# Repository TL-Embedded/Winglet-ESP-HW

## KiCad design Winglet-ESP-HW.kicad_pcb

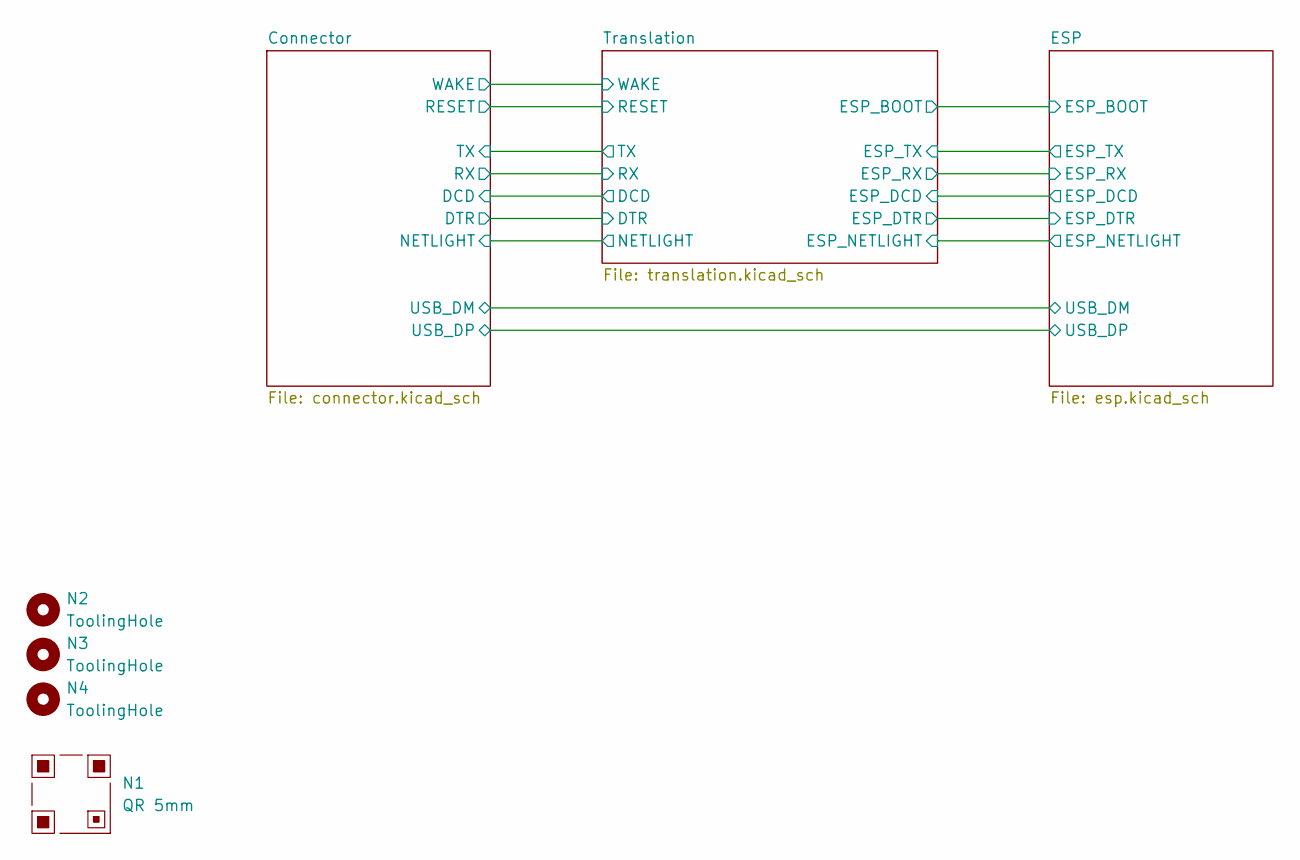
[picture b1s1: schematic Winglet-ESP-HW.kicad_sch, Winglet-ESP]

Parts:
N1: QR 5mm; QR_5mm_JLC
N2, N3, N4: ToolingHole; ToolingHole_1mm

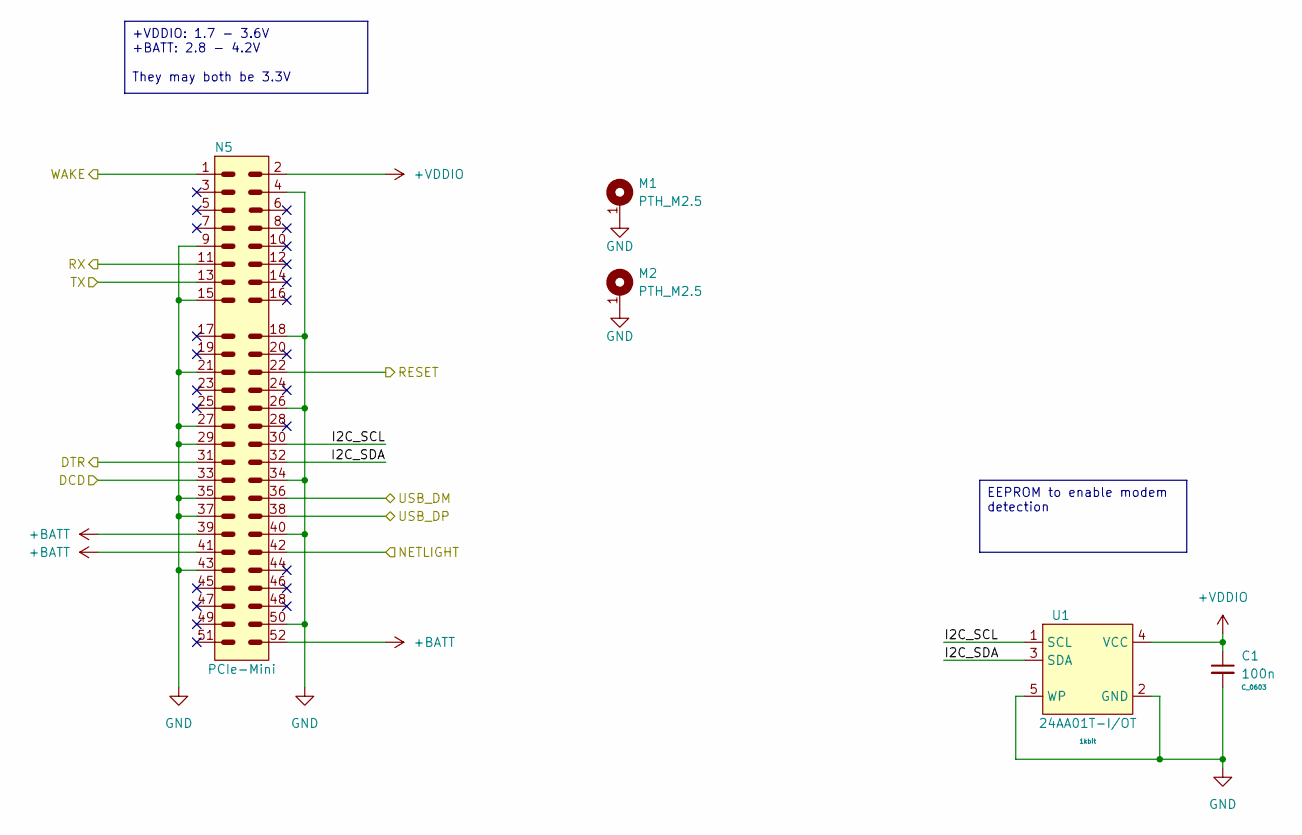
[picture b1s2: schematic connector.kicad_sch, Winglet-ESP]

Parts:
C1: 100n; C_0603
M1, M2: PTH_M2.5
N5: PCIe-Mini
U1: 24AA01T-I/OT; SOT23_5

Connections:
+BATT: N5.39, N5.41, N5.52; also elsewhere on the board
+VDDIO: C1.1, N5.2, U1.4 (VCC); also elsewhere on the board
/Connector/DCD: N5.33; also elsewhere on the board
/Connector/DTR: N5.31; also elsewhere on the board
/Connector/I2C_SCL: N5.30, U1.1 (SCL)
/Connector/I2C_SDA: N5.32, U1.3 (SDA)
/Connector/NETLIGHT: N5.42; also elsewhere on the board
/Connector/RESET: N5.22; also elsewhere on the board
/Connector/RX: N5.11; also elsewhere on the board
/Connector/TX: N5.13; also elsewhere on the board
/Connector/USB_DM: N5.36; also elsewhere on the board
/Connector/USB_DP: N5.38; also elsewhere on the board
/Connector/WAKE: N5.1; also elsewhere on the board
GND: C1.2, M1.1, M2.1, N5.4, N5.9, N5.15, N5.18, N5.21, N5.26, N5.27, N5.29, N5.34, N5.35, N5.37, N5.40, N5.43, N5.50, U1.2 (GND), U1.5 (WP); also elsewhere on the board

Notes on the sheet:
+VDDIO: 1.7 - 3.6V +BATT: 2.8 - 4.2V They may both be 3.3V
EEPROM to enable modem detection

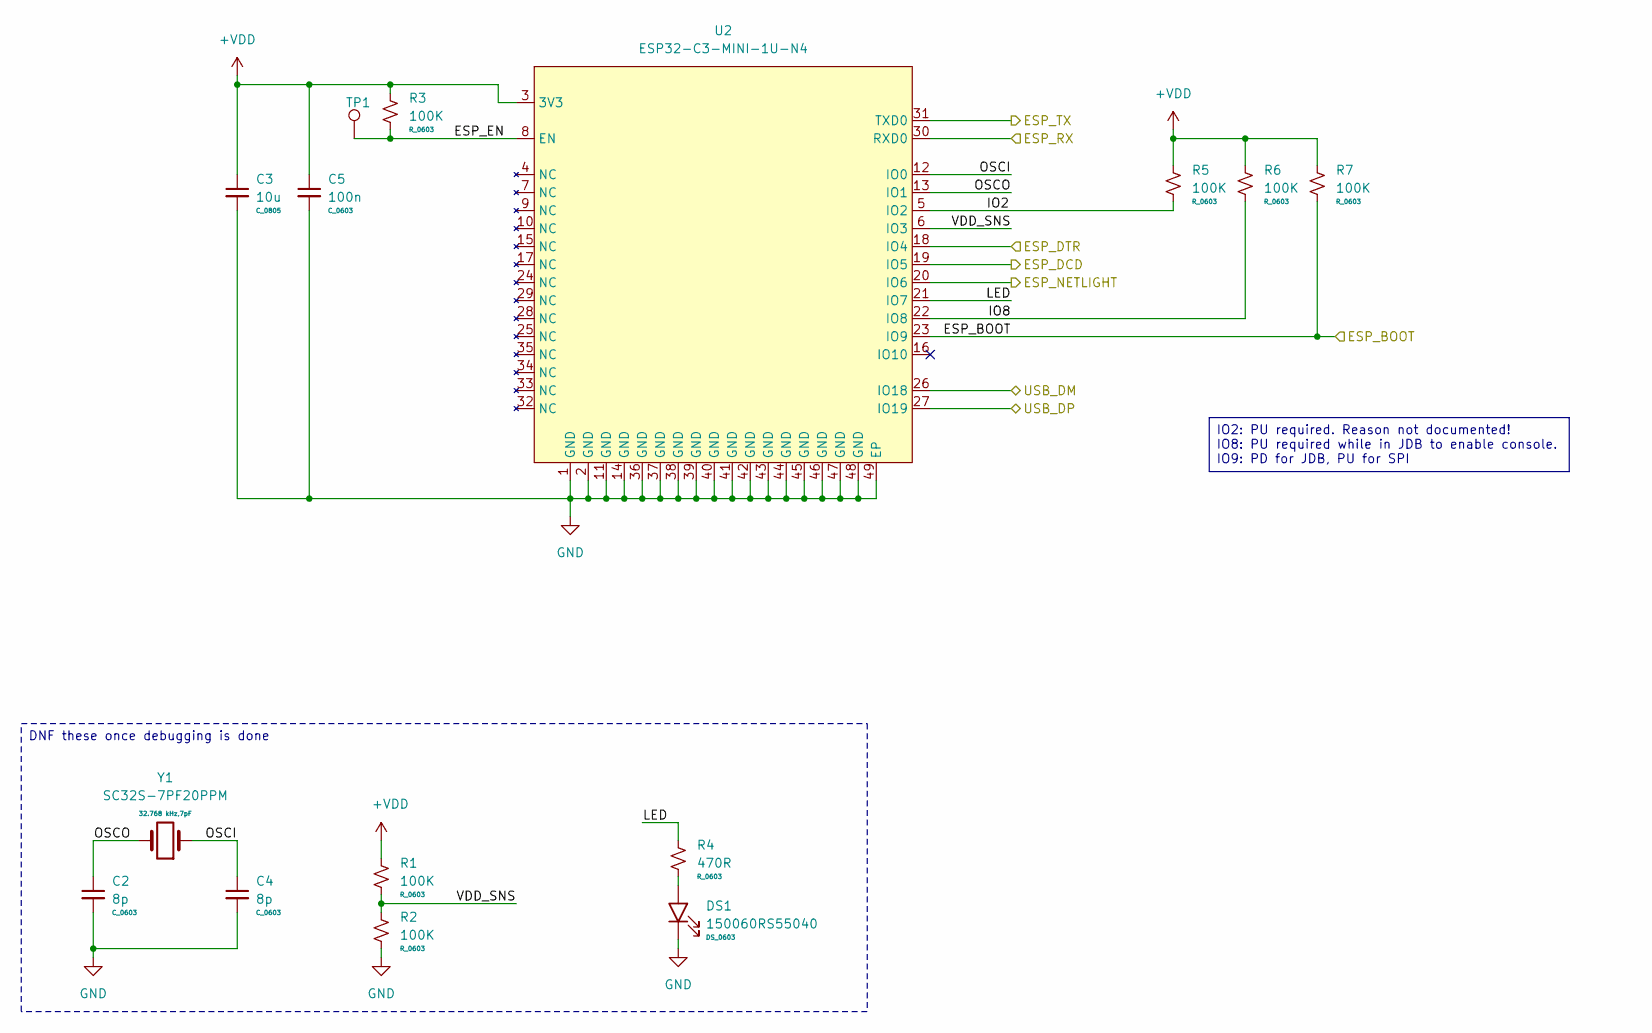
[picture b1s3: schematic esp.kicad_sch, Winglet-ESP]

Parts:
C2, C4: 8p; C_0603
C3: 10u; C_0805
C5: 100n; C_0603
DS1: 150060RS55040; DS_0603
R1, R2, R3, R5, R6, R7: 100K; R_0603
R4: 470R; R_0603
TP1: TestPoint_1mm
U2: ESP32-C3-MINI-1U-N4; ESP32-C3-MINI-1U
Y1: SC32S-7PF20PPM; Crystal_SMD2_3.2x1.5

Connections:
+VDD: C3.1, C5.1, R1.1, R3.1, R5.1, R6.1, R7.1, U2.3 (3V3); also elsewhere on the board
/Connector/USB_DM: U2.26 (IO18); also elsewhere on the board
/Connector/USB_DP: U2.27 (IO19); also elsewhere on the board
/ESP/ESP_BOOT: R7.2, U2.23 (IO9); also elsewhere on the board
/ESP/ESP_DCD: U2.19 (IO5); also elsewhere on the board
/ESP/ESP_DTR: U2.18 (IO4); also elsewhere on the board
/ESP/ESP_EN: R3.2, TP1.1, U2.8 (EN)
/ESP/ESP_NETLIGHT: U2.20 (IO6); also elsewhere on the board
/ESP/ESP_RX: U2.30 (RXD0); also elsewhere on the board
/ESP/ESP_TX: U2.31 (TXD0); also elsewhere on the board
/ESP/IO2: R5.2, U2.5 (IO2)
/ESP/IO8: R6.2, U2.22 (IO8)
/ESP/LED: R4.1, U2.21 (IO7)
/ESP/OSCI: C4.1, U2.12 (IO0), Y1.1
/ESP/OSCO: C2.1, U2.13 (IO1), Y1.2
/ESP/VDD_SNS: R1.2, R2.1, U2.6 (IO3)
GND: C2.2, C3.2, C4.2, C5.2, DS1.1 (K), R2.2, U2.1 (GND), U2.2 (GND), U2.11 (GND), U2.14 (GND), U2.36 (GND), U2.37 (GND), U2.38 (GND), U2.39 (GND), U2.40 (GND), U2.41 (GND), U2.42 (GND), U2.43 (GND), U2.44 (GND), U2.45 (GND), U2.46 (GND), U2.47 (GND), U2.48 (GND), U2.49 (EP); also elsewhere on the board
unnamed: DS1.2 (A), R4.2

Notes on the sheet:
IO2: PU required. Reason not documented! IO8: PU required while in JDB to enable console. IO9: PD for JDB, PU for SPI
DNF these once debugging is done

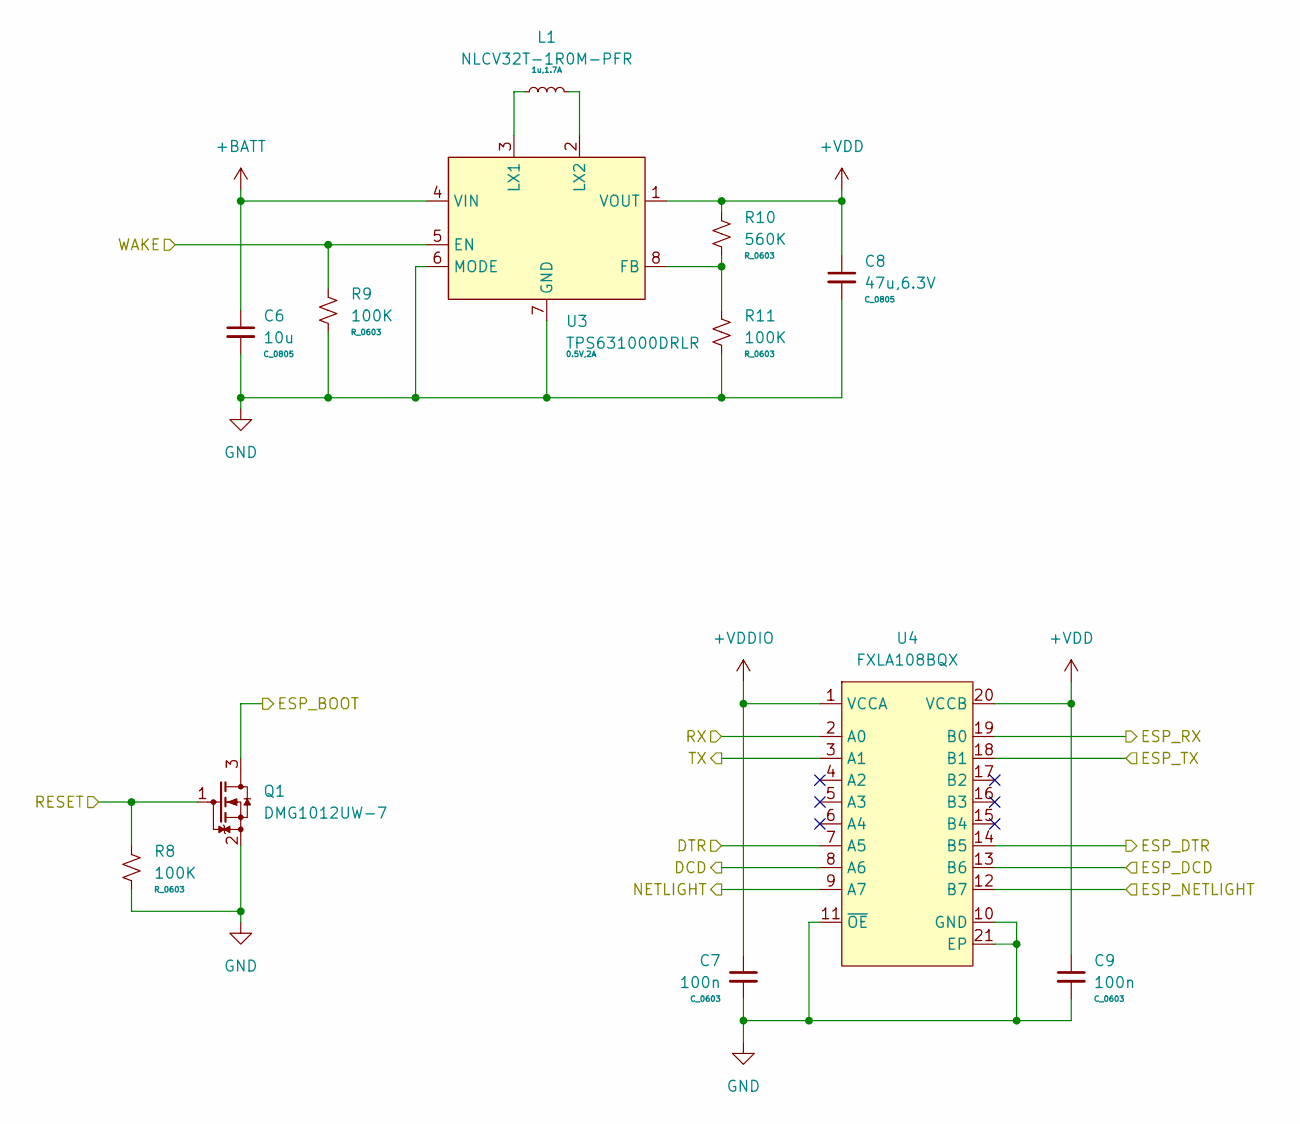
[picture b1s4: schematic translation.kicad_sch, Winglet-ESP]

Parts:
C6: 10u; C_0805
C7, C9: 100n; C_0603
C8: 47u,6.3V; C_0805
L1: NLCV32T-1R0M-PFR; L_1210
Q1: DMG1012UW-7; SC70-3
R8, R9, R11: 100K; R_0603
R10: 560K; R_0603
U3: TPS631000DRLR; SOT583
U4: FXLA108BQX; WQFN20_05_4.5x2.5

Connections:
+BATT: C6.1, U3.4 (VIN); also elsewhere on the board
+VDD: C8.1, C9.1, R10.1, U3.1 (VOUT), U4.20 (VCCB); also elsewhere on the board
+VDDIO: C7.1, U4.1 (VCCA); also elsewhere on the board
/Connector/DCD: U4.8 (A6); also elsewhere on the board
/Connector/DTR: U4.7 (A5); also elsewhere on the board
/Connector/NETLIGHT: U4.9 (A7); also elsewhere on the board
/Connector/RESET: Q1.1 (G), R8.1; also elsewhere on the board
/Connector/RX: U4.2 (A0); also elsewhere on the board
/Connector/TX: U4.3 (A1); also elsewhere on the board
/Connector/WAKE: R9.1, U3.5 (EN); also elsewhere on the board
/ESP/ESP_BOOT: Q1.3 (D); also elsewhere on the board
/ESP/ESP_DCD: U4.13 (B6); also elsewhere on the board
/ESP/ESP_DTR: U4.14 (B5); also elsewhere on the board
/ESP/ESP_NETLIGHT: U4.12 (B7); also elsewhere on the board
/ESP/ESP_RX: U4.19 (B0); also elsewhere on the board
/ESP/ESP_TX: U4.18 (B1); also elsewhere on the board
GND: C6.2, C7.2, C8.2, C9.2, Q1.2 (S), R8.2, R9.2, R11.2, U3.6 (MODE), U3.7 (GND), U4.10 (GND), U4.11 (~OE), U4.21 (EP); also elsewhere on the board
unnamed: R10.2, R11.1, U3.8 (FB)
unnamed: L1.1, U3.3 (LX1)
unnamed: L1.2, U3.2 (LX2)

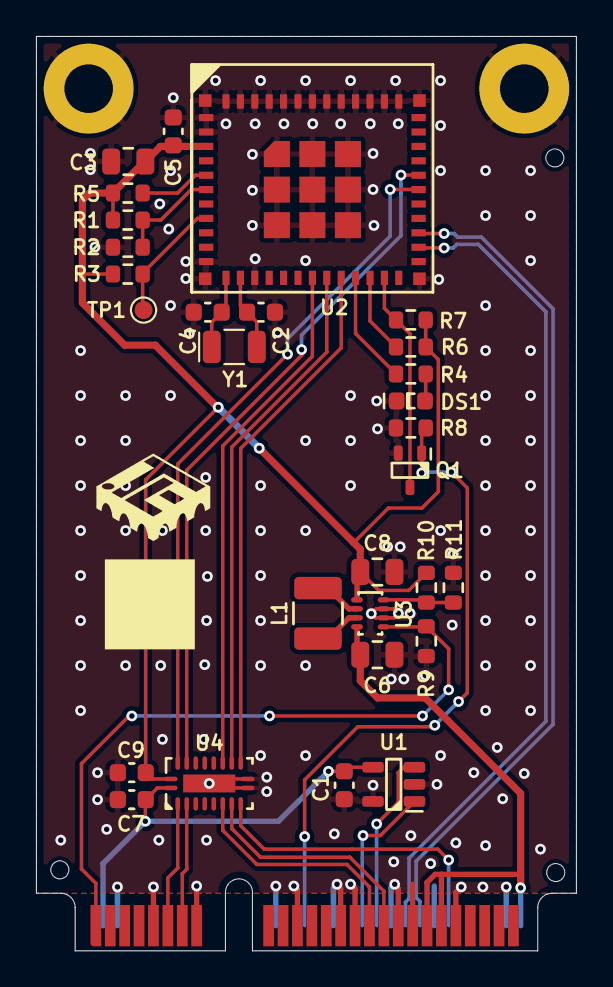
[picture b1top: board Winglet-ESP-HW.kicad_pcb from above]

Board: 2 copper layers, 30.0 x 50.8 mm, 36 parts (0 on the bottom side), 32 nets.

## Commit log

2025-06-01 First pass at ESP card
2025-06-03 Overhaul for buck-boost converter
2025-06-03 Update substitutions
2026-05-01 Steps for building AT firmware
